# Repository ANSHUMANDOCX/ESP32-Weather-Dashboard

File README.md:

# E-paper Weather Board
This is a E-ink weather dashboard made using a esp32c3 xiao and a 4.2 inch EPD. It uses OpenWeatherMap to fetch the data.
It can display the Temprature, Humidity and Weather forecast.
It fetches the Data over wifi also it is very low power and efficent.

## Parts
- 4.2 inch epaper display 
- ESP32C3 Xiao

## Schematic PCB and CAD

## BOM
|Part|Supplier|Cost|LINK|
|----|--------|----|----|
|4.2 inch EPD|ROBU|$26.98|https://robu.in/product/4-2-inch-high-refresh-rate-black-and-white-e-paper-display/|
|PCB|JLCPCB|$10.64|||
|total||$37.64||

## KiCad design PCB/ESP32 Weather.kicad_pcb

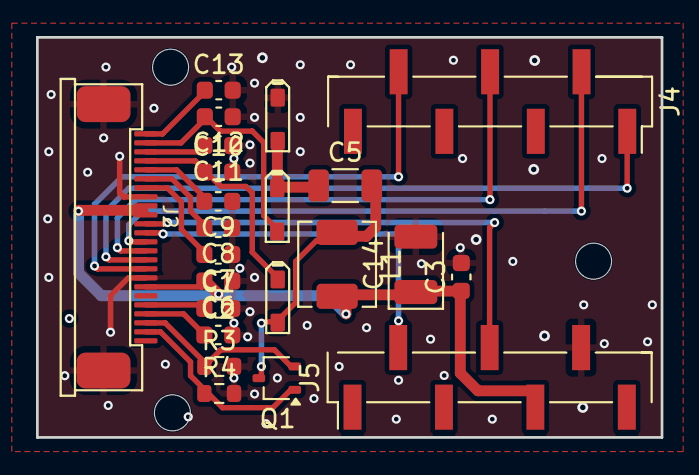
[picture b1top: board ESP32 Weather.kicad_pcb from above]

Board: 2 copper layers, 34.7 x 22.2 mm, 23 parts (0 on the bottom side), 21 nets.

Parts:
C1, C2, C3, C7, C8, C9, C10, C11, C12, C13: 1uF; C_0603_1608Metric
C5: 4.7uF/50V; C_1206_3216Metric
C6: 100nF; C_0603_1608Metric
C14: 220uF/6.3V; CP_EIA-3528-15_AVX-H
D1, D2, D3: B0540W; SOD-323
J2: Display; FPCB24-SMD-0.5-17.6X5.0X2MM
J4: Conn_01x07_Pin; PinHeader_1x07_P2.54mm_Vertical_SMD_Pin1Right
J5: Conn_01x07_Pin; PinHeader_1x07_P2.54mm_Vertical_SMD_Pin1Left
L1: 10uH; L_TechFuse_SL0420
Q1: Si1304BDL; SOT-323_SC-70
R3: 0.47R/1%; R_0603_1608Metric
R4: 10K; R_0603_1608Metric

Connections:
+3V3: C3.1, C6.2, C14.1, J2.7, J2.15, J2.16, J5.5, L1.2
D0/RST: J2.10, J4.1
D1/CS: J2.12, J4.2
D3/DC: J2.11, J4.4
D5/BUSY: J2.9, J4.6
GND: C1.2, C2.2, C3.2, C6.1, C7.1, C8.1, C9.1, C10.2, C11.1, C12.1, C13.2, C14.2, D3.-, J2.8, J2.17, J2.25 (P1), J2.26 (P2), J5.6, R3.2, R4.2
MOSI: J2.14, J5.4
unnamed: C1.1, J2.5
unnamed: C2.1, J2.4
unnamed: C5.1, D2.-, D3.+
unnamed: C7.2, J2.18
unnamed: C8.2, J2.19
unnamed: C9.2, J2.20
unnamed: C10.1, D1.-, J2.21
unnamed: C11.2, J2.22
unnamed: C12.2, D2.+, J2.23
unnamed: C13.1, J2.24
unnamed: C5.2, D1.+, L1.1, Q1.3 (D)
unnamed: J2.2, Q1.1 (G), R4.1
unnamed: J2.3, Q1.2 (S), R3.1
SCK: J2.13, J5.2

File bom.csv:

Designator,Footprint,Quantity,Value,LCSC Part #
"C1, C10, C11, C12, C13, C2, C3, C7, C8, C9",0603,10,1uF,
C14,CP_EIA-3528-15_AVX-H,1,220uF/6.3V,
C5,1206,1,4.7uF/50V,
C6,0603,1,100nF,
"D1, D2, D3",SOD-323,3,B0540W,
J2,FPCB24-SMD-0.5-17.6X5.0X2MM,1,Display,
J4,PinHeader_1x07_P2.54mm_Vertical_SMD_Pin1Right,1,Conn_01x07_Pin,
J5,PinHeader_1x07_P2.54mm_Vertical_SMD_Pin1Left,1,Conn_01x07_Pin,
L1,L_TechFuse_SL0420,1,10uH,
Q1,SOT-323_SC-70,1,Si1304BDL,
R3,0603,1,0.47R/1%,
R4,0603,1,10K,

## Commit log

2025-10-30 Update BOM with PCB and total cost
